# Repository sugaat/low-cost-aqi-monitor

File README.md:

# low-cost-aqi-monitor
esp32 based aqi monitor for pm, co, temperature and humidity

## overview
a low-cost air quality monitoring system based on esp32. the system measures pm1, pm2.5, PM10 , CO concentration , temperature and humidity.

## Hardware Used
- ESP32 Dev Module
- Planttower PMS7003
- Winsen ZE-15 CO
- DHT 22
- LCD screen

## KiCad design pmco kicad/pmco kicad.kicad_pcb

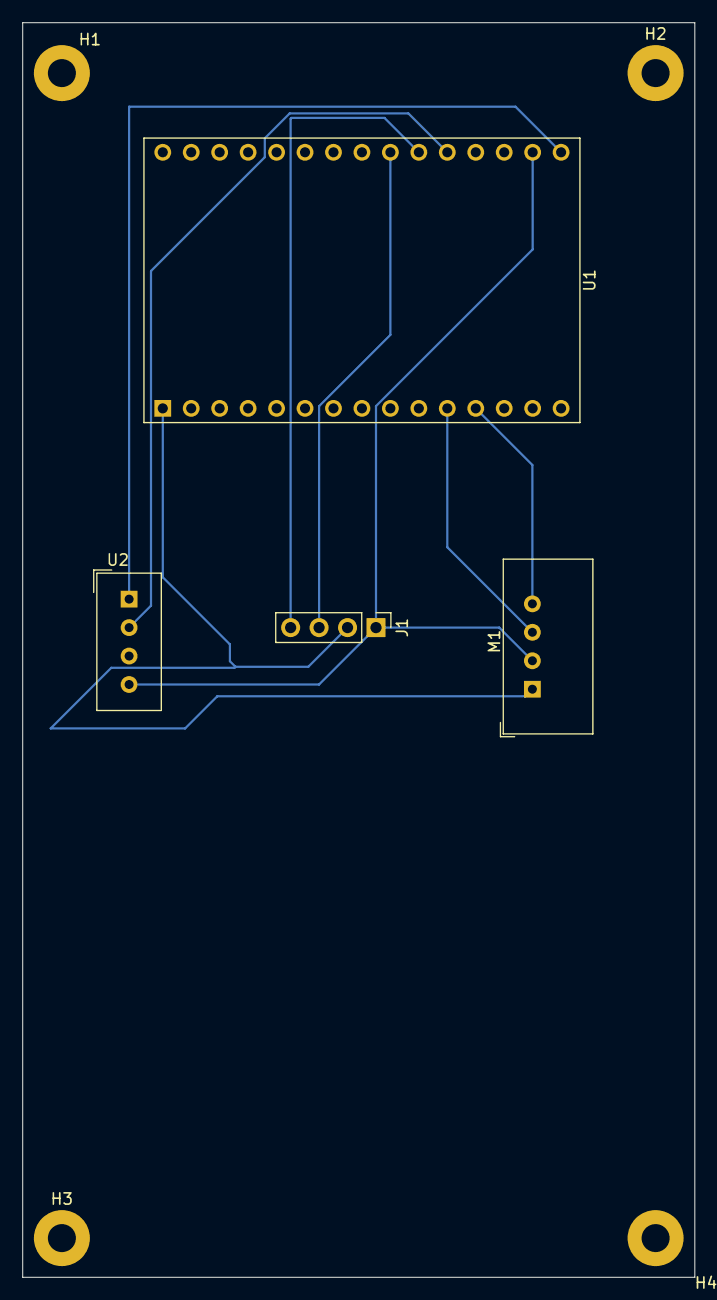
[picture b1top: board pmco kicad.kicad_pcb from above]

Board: 2 copper layers, 60.0 x 112.0 mm, 8 parts (0 on the bottom side), 8 nets.

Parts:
H1, H2, H3, H4: MountingHole; MountingHole_2.5mm_Pad
J1: PMS7003; PinHeader_1x04_P2.54mm_Vertical
M1: MQ-7; ASAIR_AM2302_P2.54mm_Vertical
U1: ESP32-C3-DevKitM-1
U2: DHT11; Aosong_DHT11_5.5x12.0_P2.54mm

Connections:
3.3V: U1.16 (3.3v), U2.1 (VCC)
5V: J1.2 (VCC), M1.1 (VCC), U1.1 (VIN)
AO: M1.4 (AO), U1.12 (GPIO34)
DATA: U1.20 (GPIO4), U2.2 (DATA)
DO: M1.3 (DO), U1.11 (GPIO35)
GND: J1.1 (GND), M1.2 (GND), U1.17 (GND), U2.4 (GND)
RX: J1.3 (RX), U1.22 (GPIO17)
TX: J1.4 (TX), U1.21 (GPIO16)

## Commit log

2026-01-18 Create code-with-display
2026-01-18 Update code-with-display
2026-02-20 kicad files backup
2026-04-17 updates firmware with live database
2026-04-17 website dashboard
